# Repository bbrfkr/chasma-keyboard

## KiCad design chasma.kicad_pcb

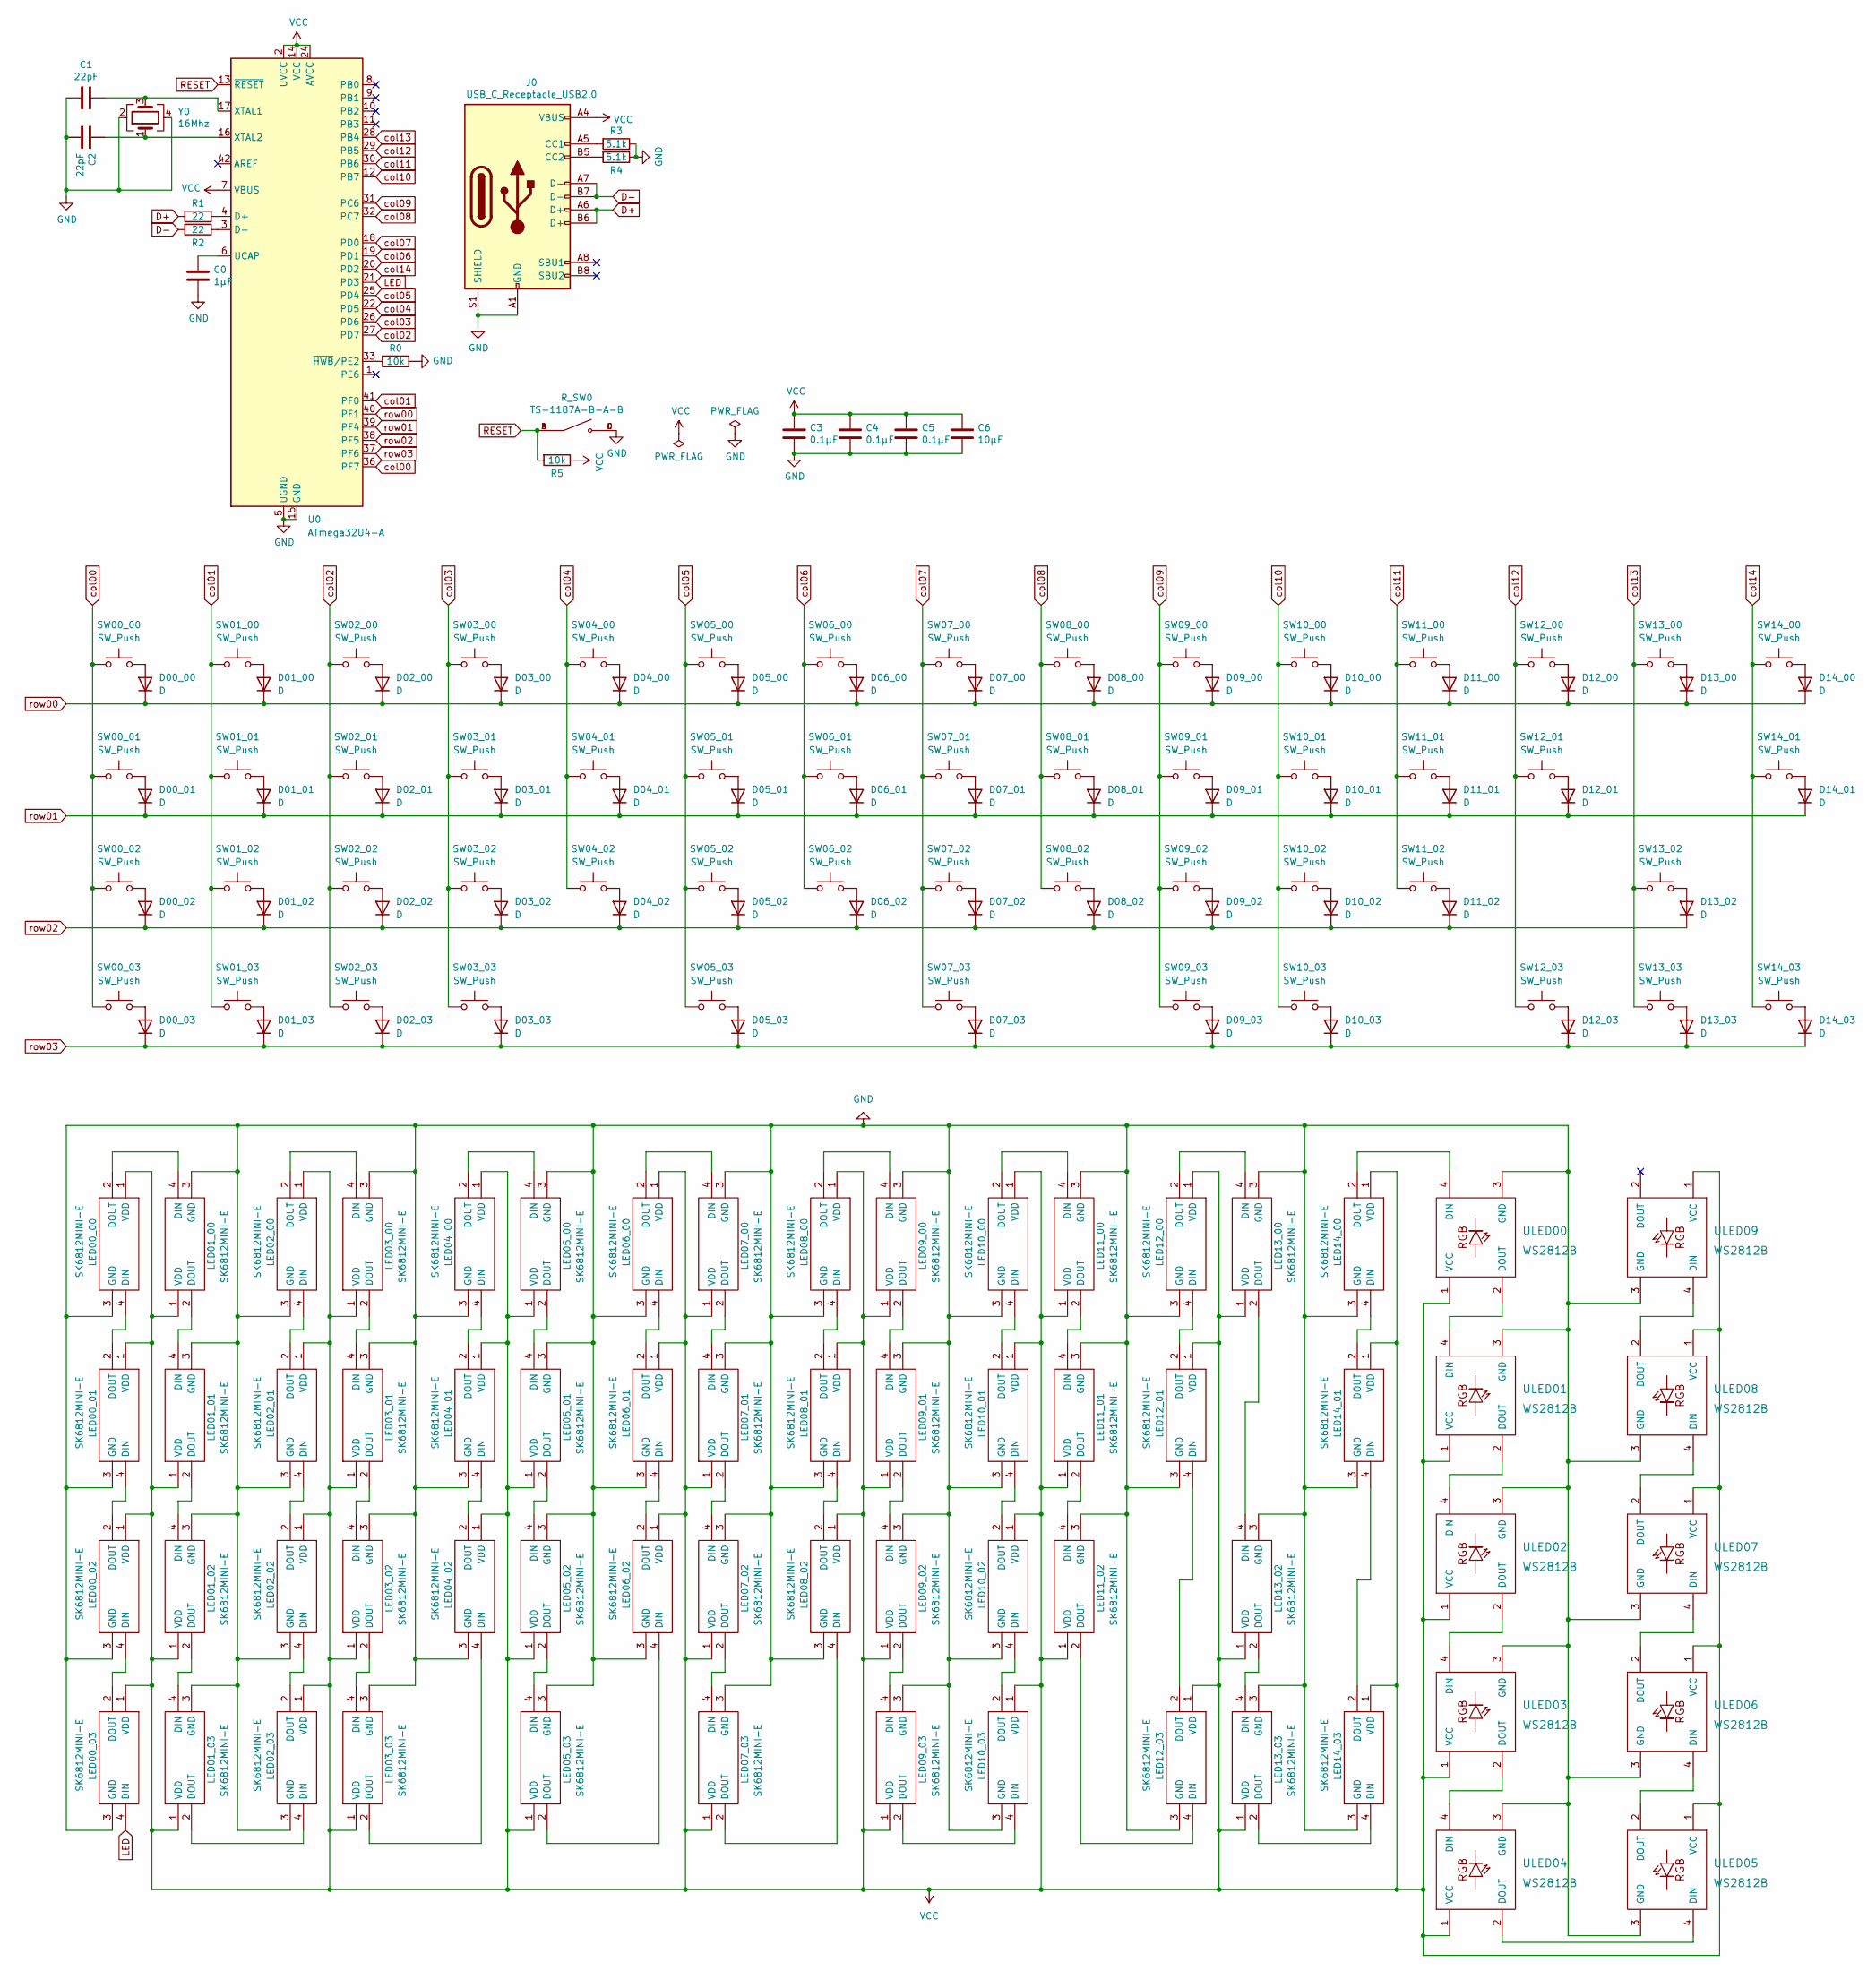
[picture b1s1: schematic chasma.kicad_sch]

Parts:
C0: 1μF; C_1206_3216Metric
C1, C2: 22pF; C_1206_3216Metric
C3, C4, C5: 0.1μF; C_1206_3216Metric
C6: 10μF; C_1206_3216Metric
D00_00, D00_01, D00_02, D00_03, D01_00, D01_01, D01_02, D01_03, D02_00, D02_01, D02_02, D02_03, D03_00, D03_01, D03_02, D03_03, D04_00, D04_01, D04_02, D05_00, D05_01, D05_02, D05_03, D06_00, D06_01, D06_02, D07_00, D07_01, D07_02, D07_03, D08_00, D08_01, D08_02, D09_00, D09_01, D09_02, D09_03, D10_00, D10_01, D10_02, D10_03, D11_00, D11_01, D11_02, D12_00, D12_01, D12_03, D13_00, D13_02, D13_03, D14_00, D14_01, D14_03: D; D_SOD-123-Pretty
J0: USB_C_Receptacle_USB2.0; USB_C_Receptacle_HRO_TYPE-C-31-M-12
LED00_00, LED00_01, LED00_02, LED00_03, LED01_00, LED01_01, LED01_02, LED01_03, LED02_00, LED02_01, LED02_02, LED02_03, LED03_00, LED03_01, LED03_02, LED03_03, LED04_00, LED04_01, LED04_02, LED05_00, LED05_01, LED05_02, LED05_03, LED06_00, LED06_01, LED06_02, LED07_00, LED07_01, LED07_02, LED07_03, LED08_00, LED08_01, LED08_02, LED09_00, LED09_01, LED09_02, LED09_03, LED10_00, LED10_01, LED10_02, LED10_03, LED11_00, LED11_01, LED11_02, LED12_00, LED12_01, LED12_03, LED13_00, LED13_02, LED13_03, LED14_00, LED14_01, LED14_03: SK6812MINI-E; SK6812MINIE; Manufacturer_Part_Number SK6812MINI-E
R0, R5: 10k; R_1206_3216Metric
R1, R2: 22; R_1206_3216Metric
R3, R4: 5.1k; R_1206_3216Metric
R_SW0: TS-1187A-B-A-B; SW_TS-1187A-B-A-B; PARTREV A0
SW00_00, SW13_00: SW_Push; MXOnly-1.5U-Hotswap
SW00_01, SW11_02: SW_Push; MXOnly-1.75U-Hotswap
SW00_02: SW_Push; MXOnly-2.25U-Hotswap
SW00_03, SW01_03, SW02_03, SW05_03, SW09_03, SW10_03: SW_Push; MXOnly-1.25U-Hotswap
SW01_00, SW01_01, SW01_02, SW02_00, SW02_01, SW02_02, SW03_00, SW03_01, SW03_02, SW04_00, SW04_01, SW04_02, SW05_00, SW05_01, SW05_02, SW06_00, SW06_01, SW06_02, SW07_00, SW07_01, SW07_02, SW08_00, SW08_01, SW08_02, SW09_00, SW09_01, SW09_02, SW10_00, SW10_01, SW10_02, SW11_00, SW11_01, SW12_00, SW12_03, SW13_02, SW13_03, SW14_00, SW14_01, SW14_03: SW_Push; MXOnly-1U-Hotswap
SW03_03, SW12_01: SW_Push; MXOnly-2.25U-Hotswap-ReversedStabilizers
SW07_03: SW_Push; MXOnly-2.75U-Hotswap-ReversedStabilizers
U0: ATmega32U4-A; TQFP-44_10x10mm_P0.8mm
ULED00, ULED01, ULED02, ULED03, ULED04, ULED05, ULED06, ULED07, ULED08, ULED09: WS2812B
Y0: 16Mhz; Crystal_SMD_SeikoEpson_FA238-4Pin_3.2x2.5mm

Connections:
D+: J0.A6 (D+), J0.B6 (D+), R1.2
D-: J0.A7 (D-), J0.B7 (D-), R2.2
GND: C0.2, C1.1, C2.2, C3.2, C4.2, C5.2, C6.2, J0.A1 (GND), J0.A12 (GND), J0.B1 (GND), J0.B12 (GND), J0.S1 (SHIELD), LED00_00.3 (GND), LED00_01.3 (GND), LED00_02.3 (GND), LED00_03.3 (GND), LED01_00.3 (GND), LED01_01.3 (GND), LED01_02.3 (GND), LED01_03.3 (GND), LED02_00.3 (GND), LED02_01.3 (GND), LED02_02.3 (GND), LED02_03.3 (GND), LED03_00.3 (GND), LED03_01.3 (GND), LED03_02.3 (GND), LED03_03.3 (GND), LED04_00.3 (GND), LED04_01.3 (GND), LED04_02.3 (GND), LED05_00.3 (GND), LED05_01.3 (GND), LED05_02.3 (GND), LED05_03.3 (GND), LED06_00.3 (GND), LED06_01.3 (GND), LED06_02.3 (GND), LED07_00.3 (GND), LED07_01.3 (GND), LED07_02.3 (GND), LED07_03.3 (GND), LED08_00.3 (GND), LED08_01.3 (GND), LED08_02.3 (GND), LED09_00.3 (GND), LED09_01.3 (GND), LED09_02.3 (GND), LED09_03.3 (GND), LED10_00.3 (GND), LED10_01.3 (GND), LED10_02.3 (GND), LED10_03.3 (GND), LED11_00.3 (GND), LED11_01.3 (GND), LED11_02.3 (GND), LED12_00.3 (GND), LED12_01.3 (GND), LED12_03.3 (GND), LED13_00.3 (GND), LED13_02.3 (GND), LED13_03.3 (GND), LED14_00.3 (GND), LED14_01.3 (GND), LED14_03.3 (GND), R0.1, R3.1, R4.1, R_SW0.C, R_SW0.D, U0.5 (UGND), U0.15 (GND), U0.23 (GND), U0.35 (GND), U0.43 (GND), ULED00.3 (GND), ULED01.3 (GND), ULED02.3 (GND), ULED03.3 (GND), ULED04.3 (GND), ULED05.3 (GND), ULED06.3 (GND), ULED07.3 (GND), ULED08.3 (GND), ULED09.3 (GND), Y0.2, Y0.4
LED: LED00_03.4 (DIN), U0.21 (PD3)
unnamed: C0.1, U0.6 (UCAP)
unnamed: C1.2, U0.17 (XTAL1), Y0.3
unnamed: C2.1, U0.16 (XTAL2), Y0.1
unnamed: D00_00.2 (A), SW00_00.2
unnamed: D00_01.2 (A), SW00_01.2
unnamed: D00_02.2 (A), SW00_02.2
unnamed: D00_03.2 (A), SW00_03.2
unnamed: D01_00.2 (A), SW01_00.2
unnamed: D01_01.2 (A), SW01_01.2
unnamed: D01_02.2 (A), SW01_02.2
unnamed: D01_03.2 (A), SW01_03.2
unnamed: D02_00.2 (A), SW02_00.2
unnamed: D02_01.2 (A), SW02_01.2
unnamed: D02_02.2 (A), SW02_02.2
unnamed: D02_03.2 (A), SW02_03.2
unnamed: D03_00.2 (A), SW03_00.2
unnamed: D03_01.2 (A), SW03_01.2
unnamed: D03_02.2 (A), SW03_02.2
unnamed: D03_03.2 (A), SW03_03.2
unnamed: D04_00.2 (A), SW04_00.2
unnamed: D04_01.2 (A), SW04_01.2
unnamed: D04_02.2 (A), SW04_02.2
unnamed: D05_00.2 (A), SW05_00.2
unnamed: D05_01.2 (A), SW05_01.2
unnamed: D05_02.2 (A), SW05_02.2
unnamed: D05_03.2 (A), SW05_03.2
unnamed: D06_00.2 (A), SW06_00.2
unnamed: D06_01.2 (A), SW06_01.2
unnamed: D06_02.2 (A), SW06_02.2
unnamed: D07_00.2 (A), SW07_00.2
unnamed: D07_01.2 (A), SW07_01.2
unnamed: D07_02.2 (A), SW07_02.2
unnamed: D07_03.2 (A), SW07_03.2
unnamed: D08_00.2 (A), SW08_00.2
unnamed: D08_01.2 (A), SW08_01.2
unnamed: D08_02.2 (A), SW08_02.2
unnamed: D09_00.2 (A), SW09_00.2
unnamed: D09_01.2 (A), SW09_01.2
unnamed: D09_02.2 (A), SW09_02.2
unnamed: D09_03.2 (A), SW09_03.2
unnamed: D10_00.2 (A), SW10_00.2
unnamed: D10_01.2 (A), SW10_01.2
unnamed: D10_02.2 (A), SW10_02.2
unnamed: D10_03.2 (A), SW10_03.2
unnamed: D11_00.2 (A), SW11_00.2
unnamed: D11_01.2 (A), SW11_01.2
unnamed: D11_02.2 (A), SW11_02.2
unnamed: D12_00.2 (A), SW12_00.2
unnamed: D12_01.2 (A), SW12_01.2
unnamed: D12_03.2 (A), SW12_03.2
unnamed: D13_00.2 (A), SW13_00.2
unnamed: D13_02.2 (A), SW13_02.2
unnamed: D13_03.2 (A), SW13_03.2
unnamed: D14_00.2 (A), SW14_00.2
unnamed: D14_01.2 (A), SW14_01.2
unnamed: D14_03.2 (A), SW14_03.2
unnamed: J0.A5 (CC1), R3.2
unnamed: J0.B5 (CC2), R4.2
unnamed: LED00_00.2 (DOUT), LED01_00.4 (DIN)
unnamed: LED00_00.4 (DIN), LED00_01.2 (DOUT)
unnamed: LED00_01.4 (DIN), LED00_02.2 (DOUT)
unnamed: LED00_02.4 (DIN), LED00_03.2 (DOUT)
unnamed: LED01_00.2 (DOUT), LED01_01.4 (DIN)
unnamed: LED01_01.2 (DOUT), LED01_02.4 (DIN)
unnamed: LED01_02.2 (DOUT), LED01_03.4 (DIN)
unnamed: LED01_03.2 (DOUT), LED02_03.4 (DIN)
unnamed: LED02_00.2 (DOUT), LED03_00.4 (DIN)
unnamed: LED02_00.4 (DIN), LED02_01.2 (DOUT)
unnamed: LED02_01.4 (DIN), LED02_02.2 (DOUT)
unnamed: LED02_02.4 (DIN), LED02_03.2 (DOUT)
unnamed: LED03_00.2 (DOUT), LED03_01.4 (DIN)
unnamed: LED03_01.2 (DOUT), LED03_02.4 (DIN)
unnamed: LED03_02.2 (DOUT), LED03_03.4 (DIN)
unnamed: LED03_03.2 (DOUT), LED04_02.4 (DIN)
unnamed: LED04_00.2 (DOUT), LED05_00.4 (DIN)
unnamed: LED04_00.4 (DIN), LED04_01.2 (DOUT)
unnamed: LED04_01.4 (DIN), LED04_02.2 (DOUT)
unnamed: LED05_00.2 (DOUT), LED05_01.4 (DIN)
unnamed: LED05_01.2 (DOUT), LED05_02.4 (DIN)
unnamed: LED05_02.2 (DOUT), LED05_03.4 (DIN)
unnamed: LED05_03.2 (DOUT), LED06_02.4 (DIN)
unnamed: LED06_00.2 (DOUT), LED07_00.4 (DIN)
unnamed: LED06_00.4 (DIN), LED06_01.2 (DOUT)
unnamed: LED06_01.4 (DIN), LED06_02.2 (DOUT)
unnamed: LED07_00.2 (DOUT), LED07_01.4 (DIN)
unnamed: LED07_01.2 (DOUT), LED07_02.4 (DIN)
unnamed: LED07_02.2 (DOUT), LED07_03.4 (DIN)
unnamed: LED07_03.2 (DOUT), LED08_02.4 (DIN)
unnamed: LED08_00.2 (DOUT), LED09_00.4 (DIN)
unnamed: LED08_00.4 (DIN), LED08_01.2 (DOUT)
unnamed: LED08_01.4 (DIN), LED08_02.2 (DOUT)
unnamed: LED09_00.2 (DOUT), LED09_01.4 (DIN)
unnamed: LED09_01.2 (DOUT), LED09_02.4 (DIN)
unnamed: LED09_02.2 (DOUT), LED09_03.4 (DIN)
unnamed: LED09_03.2 (DOUT), LED10_03.4 (DIN)
unnamed: LED10_00.2 (DOUT), LED11_00.4 (DIN)
unnamed: LED10_00.4 (DIN), LED10_01.2 (DOUT)
unnamed: LED10_01.4 (DIN), LED10_02.2 (DOUT)
unnamed: LED10_02.4 (DIN), LED10_03.2 (DOUT)
unnamed: LED11_00.2 (DOUT), LED11_01.4 (DIN)
unnamed: LED11_01.2 (DOUT), LED11_02.4 (DIN)
unnamed: LED11_02.2 (DOUT), LED12_03.4 (DIN)
unnamed: LED12_00.2 (DOUT), LED13_00.4 (DIN)
unnamed: LED12_00.4 (DIN), LED12_01.2 (DOUT)
unnamed: LED12_01.4 (DIN), LED12_03.2 (DOUT)
unnamed: LED13_00.2 (DOUT), LED13_02.4 (DIN)
unnamed: LED13_02.2 (DOUT), LED13_03.4 (DIN)
unnamed: LED13_03.2 (DOUT), LED14_03.4 (DIN)
unnamed: LED14_00.2 (DOUT), ULED00.4 (DIN)
unnamed: LED14_00.4 (DIN), LED14_01.2 (DOUT)
unnamed: LED14_01.4 (DIN), LED14_03.2 (DOUT)
unnamed: R0.2, U0.33 (~HWB/PE2)
unnamed: R1.1, U0.4 (D+)
unnamed: R2.1, U0.3 (D-)
unnamed: ULED00.2 (DOUT), ULED01.4 (DIN)
unnamed: ULED01.2 (DOUT), ULED02.4 (DIN)
unnamed: ULED02.2 (DOUT), ULED03.4 (DIN)
unnamed: ULED03.2 (DOUT), ULED04.4 (DIN)
unnamed: ULED04.2 (DOUT), ULED05.4 (DIN)
unnamed: ULED05.2 (DOUT), ULED06.4 (DIN)
unnamed: ULED06.2 (DOUT), ULED07.4 (DIN)
unnamed: ULED07.2 (DOUT), ULED08.4 (DIN)
unnamed: ULED08.2 (DOUT), ULED09.4 (DIN)
RESET: R5.2, R_SW0.A, R_SW0.B, U0.13 (~RESET)
VCC: C3.1, C4.1, C5.1, C6.1, J0.A4 (VBUS), J0.A9 (VBUS), J0.B4 (VBUS), J0.B9 (VBUS), LED00_00.1 (VDD), LED00_01.1 (VDD), LED00_02.1 (VDD), LED00_03.1 (VDD), LED01_00.1 (VDD), LED01_01.1 (VDD), LED01_02.1 (VDD), LED01_03.1 (VDD), LED02_00.1 (VDD), LED02_01.1 (VDD), LED02_02.1 (VDD), LED02_03.1 (VDD), LED03_00.1 (VDD), LED03_01.1 (VDD), LED03_02.1 (VDD), LED03_03.1 (VDD), LED04_00.1 (VDD), LED04_01.1 (VDD), LED04_02.1 (VDD), LED05_00.1 (VDD), LED05_01.1 (VDD), LED05_02.1 (VDD), LED05_03.1 (VDD), LED06_00.1 (VDD), LED06_01.1 (VDD), LED06_02.1 (VDD), LED07_00.1 (VDD), LED07_01.1 (VDD), LED07_02.1 (VDD), LED07_03.1 (VDD), LED08_00.1 (VDD), LED08_01.1 (VDD), LED08_02.1 (VDD), LED09_00.1 (VDD), LED09_01.1 (VDD), LED09_02.1 (VDD), LED09_03.1 (VDD), LED10_00.1 (VDD), LED10_01.1 (VDD), LED10_02.1 (VDD), LED10_03.1 (VDD), LED11_00.1 (VDD), LED11_01.1 (VDD), LED11_02.1 (VDD), LED12_00.1 (VDD), LED12_01.1 (VDD), LED12_03.1 (VDD), LED13_00.1 (VDD), LED13_02.1 (VDD), LED13_03.1 (VDD), LED14_00.1 (VDD), LED14_01.1 (VDD), LED14_03.1 (VDD), R5.1, U0.2 (UVCC), U0.7 (VBUS), U0.14 (VCC), U0.24 (AVCC), U0.34 (VCC), U0.44 (AVCC), ULED00.1 (VCC), ULED01.1 (VCC), ULED02.1 (VCC), ULED03.1 (VCC), ULED04.1 (VCC), ULED05.1 (VCC), ULED06.1 (VCC), ULED07.1 (VCC), ULED08.1 (VCC), ULED09.1 (VCC)
col00: SW00_00.1, SW00_01.1, SW00_02.1, SW00_03.1, U0.36 (PF7)
col01: SW01_00.1, SW01_01.1, SW01_02.1, SW01_03.1, U0.41 (PF0)
col02: SW02_00.1, SW02_01.1, SW02_02.1, SW02_03.1, U0.27 (PD7)
col03: SW03_00.1, SW03_01.1, SW03_02.1, SW03_03.1, U0.26 (PD6)
col04: SW04_00.1, SW04_01.1, SW04_02.1, U0.22 (PD5)
col05: SW05_00.1, SW05_01.1, SW05_02.1, SW05_03.1, U0.25 (PD4)
col06: SW06_00.1, SW06_01.1, SW06_02.1, U0.19 (PD1)
col07: SW07_00.1, SW07_01.1, SW07_02.1, SW07_03.1, U0.18 (PD0)
col08: SW08_00.1, SW08_01.1, SW08_02.1, U0.32 (PC7)
col09: SW09_00.1, SW09_01.1, SW09_02.1, SW09_03.1, U0.31 (PC6)
col10: SW10_00.1, SW10_01.1, SW10_02.1, SW10_03.1, U0.12 (PB7)
col11: SW11_00.1, SW11_01.1, SW11_02.1, U0.30 (PB6)
col12: SW12_00.1, SW12_01.1, SW12_03.1, U0.29 (PB5)
col13: SW13_00.1, SW13_02.1, SW13_03.1, U0.28 (PB4)
col14: SW14_00.1, SW14_01.1, SW14_03.1, U0.20 (PD2)
row00: D00_00.1 (K), D01_00.1 (K), D02_00.1 (K), D03_00.1 (K), D04_00.1 (K), D05_00.1 (K), D06_00.1 (K), D07_00.1 (K), D08_00.1 (K), D09_00.1 (K), D10_00.1 (K), D11_00.1 (K), D12_00.1 (K), D13_00.1 (K), D14_00.1 (K), U0.40 (PF1)
row01: D00_01.1 (K), D01_01.1 (K), D02_01.1 (K), D03_01.1 (K), D04_01.1 (K), D05_01.1 (K), D06_01.1 (K), D07_01.1 (K), D08_01.1 (K), D09_01.1 (K), D10_01.1 (K), D11_01.1 (K), D12_01.1 (K), D14_01.1 (K), U0.39 (PF4)
row02: D00_02.1 (K), D01_02.1 (K), D02_02.1 (K), D03_02.1 (K), D04_02.1 (K), D05_02.1 (K), D06_02.1 (K), D07_02.1 (K), D08_02.1 (K), D09_02.1 (K), D10_02.1 (K), D11_02.1 (K), D13_02.1 (K), U0.38 (PF5)
row03: D00_03.1 (K), D01_03.1 (K), D02_03.1 (K), D03_03.1 (K), D05_03.1 (K), D07_03.1 (K), D09_03.1 (K), D10_03.1 (K), D12_03.1 (K), D13_03.1 (K), D14_03.1 (K), U0.37 (PF6)

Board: 2 copper layers, 186 parts (80 on the bottom side), 148 nets, no tracks yet.

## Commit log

2022-11-06 initial pcb
2022-12-28 add case
2023-01-03 create pcb
2023-01-21 mod case
2023-02-12 mod pcb
2023-04-27 add firmware and foam data
2023-04-27 Initial (#1)
